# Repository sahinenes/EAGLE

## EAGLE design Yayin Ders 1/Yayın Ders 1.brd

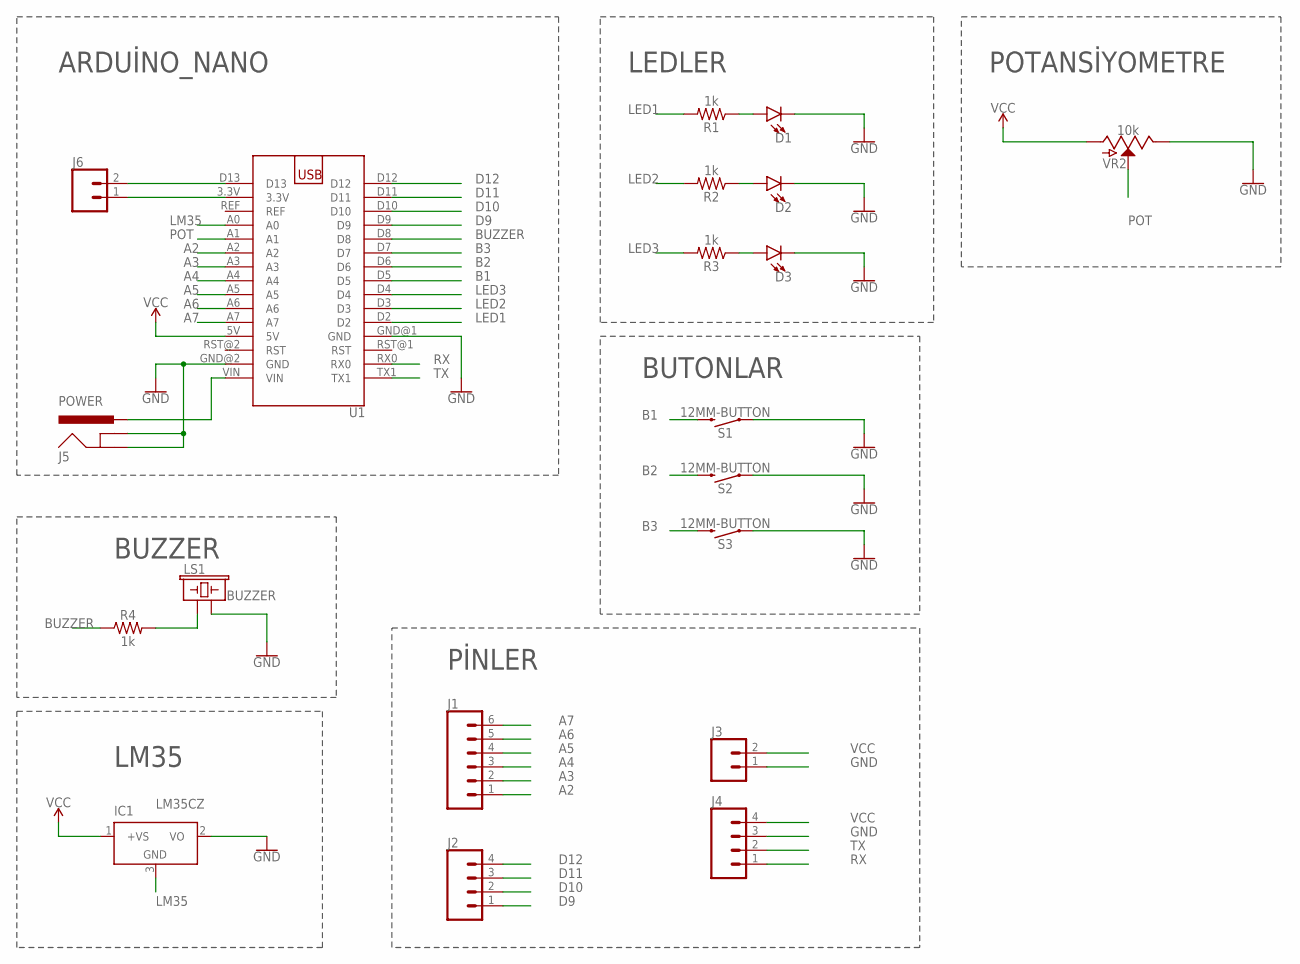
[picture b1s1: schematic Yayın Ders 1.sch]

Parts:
D1, D2, D3: LED-3MM-NO_SILK; LED_3MM-NS
IC1: LM35CZ; TO92
J1: CONN_06LOCK; 1X06_LOCK
J2, J4: CONN_04; 1X04
J3, J6: CONN_02; 1X02
J5: POWER; POWER_JACK_PTH
LS1: BUZZER; BUZZER-12MM
R1, R2, R3, R4: 1k; AXIAL-0.3
S1, S2, S3: 12MM-BUTTON; TACTILE_SWITCH_PTH_12MM
U1: ARDUINO_NANO
VR2: 10k; POT-PTH-ALPS

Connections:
A2: J1.1, U1.A2
A3: J1.2, U1.A3
A4: J1.3, U1.A4
A5: J1.4, U1.A5
A6: J1.5, U1.A6
A7: J1.6, U1.A7
B1: S1.3 (2), U1.D5
B2: S2.3 (2), U1.D6
B3: S3.3 (2), U1.D7
BUZZER: R4.P$1 (1), U1.D8
D9: J2.1, U1.D9
D10: J2.2, U1.D10
D11: J2.3, U1.D11
D12: J2.4, U1.D12
GND: D1.K (C), D2.K (C), D3.K (C), IC1.2 (VO), J3.1, J4.3, J5.GND, J5.GNDBREAK, LS1.- (2), S1.1, S2.1, S3.1, U1.GND@1 (GND), U1.GND@2 (GND), VR2.P$1 (E)
LED1: R1.P$2 (2), U1.D2
LED2: R2.P$2 (2), U1.D3
LED3: R3.P$2 (2), U1.D4
LM35: IC1.3 (GND), U1.A0
unnamed: J5.PWR, U1.VIN
unnamed: J6.2, U1.D13
unnamed: J6.1, U1.3.3V
unnamed: LS1.+ (1), R4.P$2 (2)
unnamed: D1.A, R1.P$1 (1)
unnamed: D2.A, R2.P$1 (1)
unnamed: D3.A, R3.P$1 (1)
POT: U1.A1, VR2.P$2 (S)
RX: J4.1, U1.RX0
TX: J4.2, U1.TX1
VCC: IC1.1 (+VS), J3.2, J4.4, U1.5V, VR2.P$3 (A)

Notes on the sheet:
ARDUİNO_NANO
LEDLER
BUTONLAR
PİNLER
BUZZER
LM35
POTANSİYOMETRE

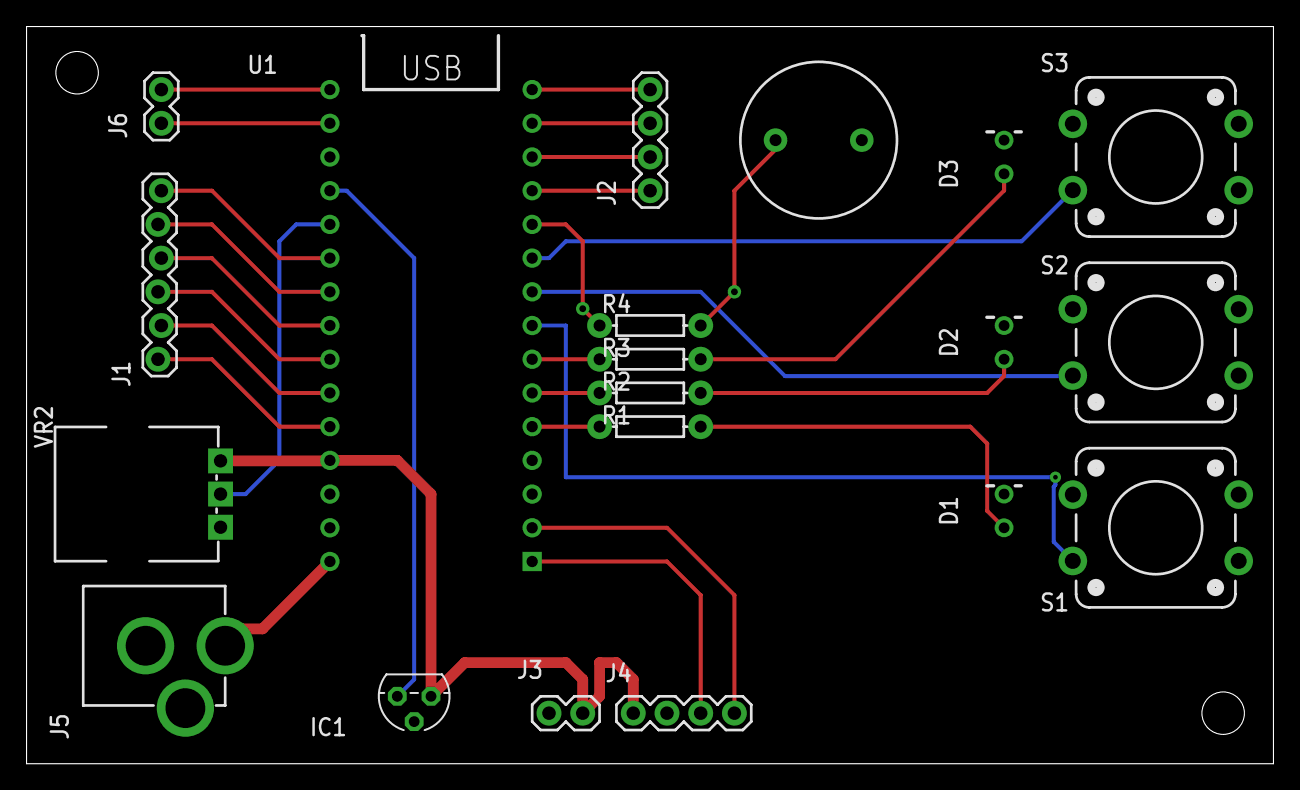
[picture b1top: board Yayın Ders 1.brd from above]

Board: 2 copper layers, 94.0 x 55.5 mm, 20 parts (0 on the bottom side), 30 nets.

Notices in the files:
parts and their libraries:
SparkFun-LED: Licensing: Creative Commons ShareAlike 4.0 International - https://creativecommons.org/licenses/by-sa/4.0
